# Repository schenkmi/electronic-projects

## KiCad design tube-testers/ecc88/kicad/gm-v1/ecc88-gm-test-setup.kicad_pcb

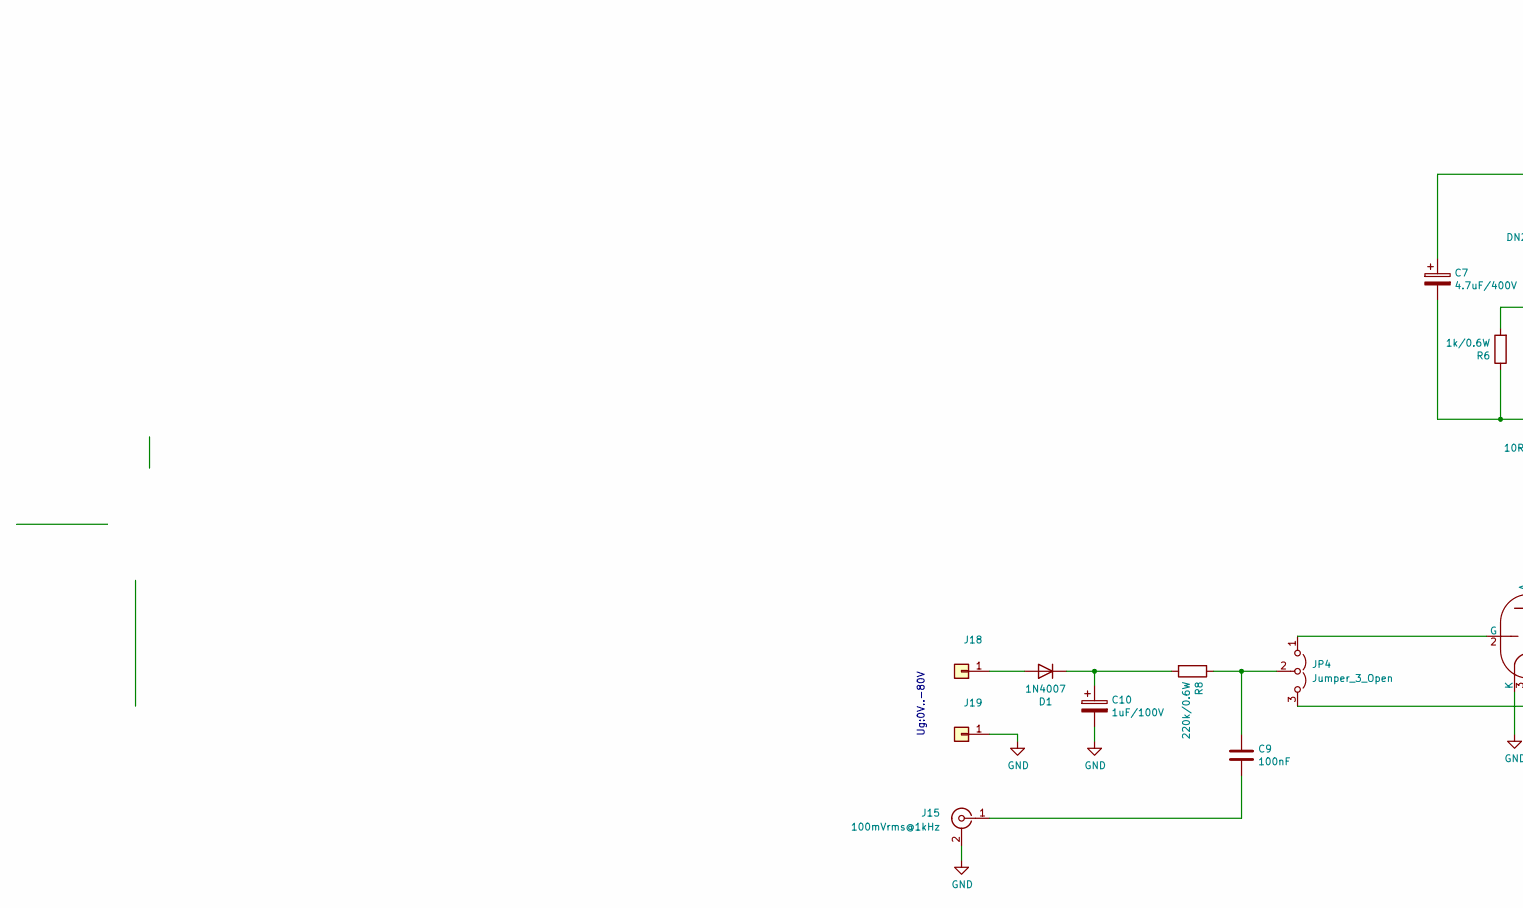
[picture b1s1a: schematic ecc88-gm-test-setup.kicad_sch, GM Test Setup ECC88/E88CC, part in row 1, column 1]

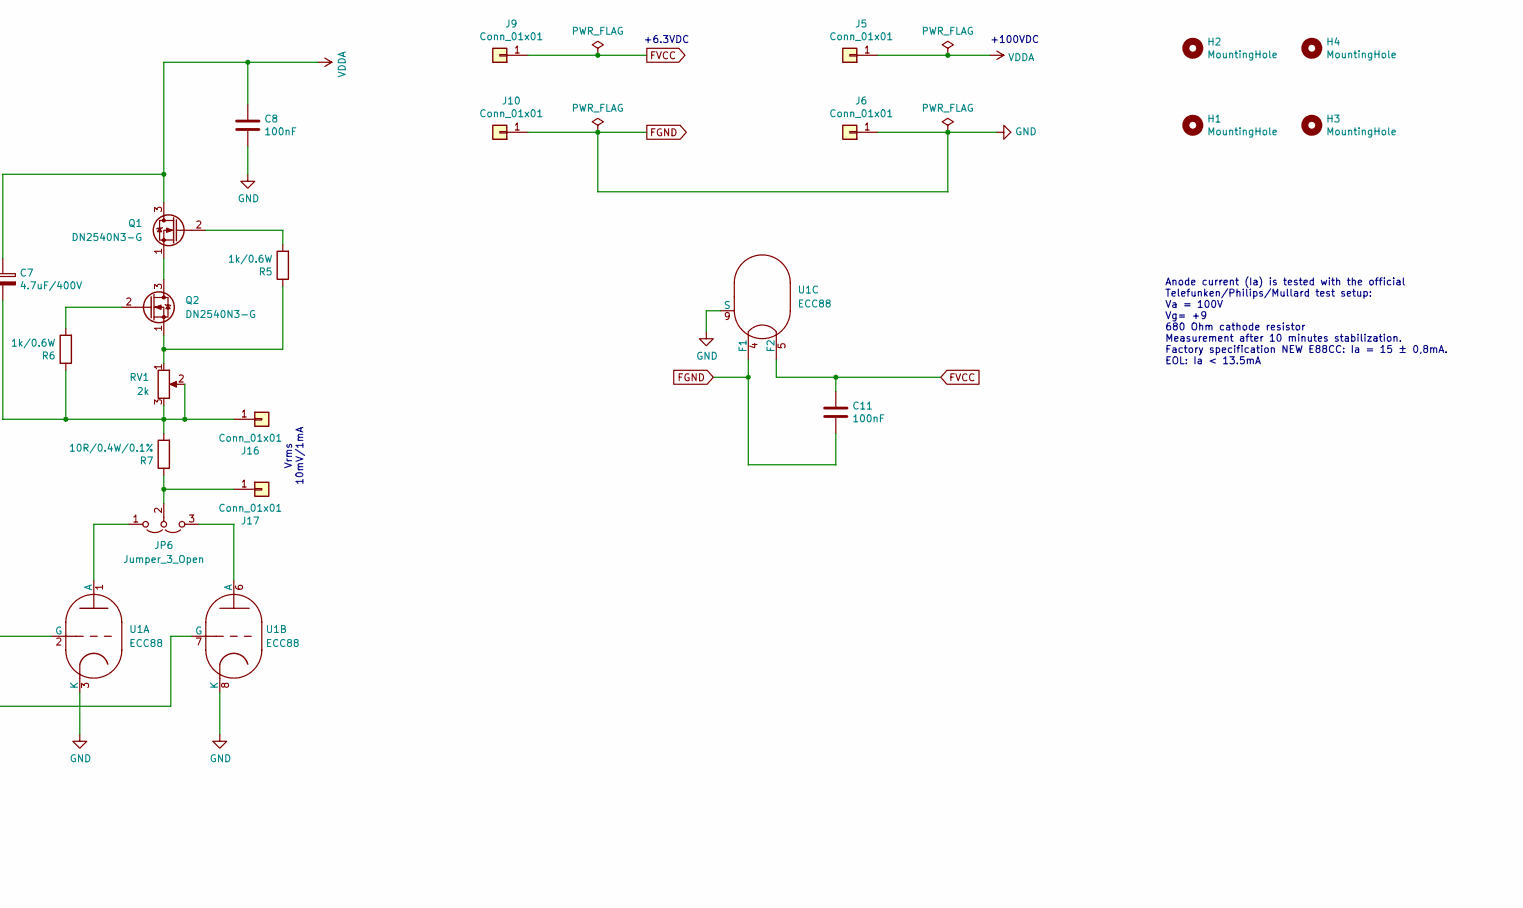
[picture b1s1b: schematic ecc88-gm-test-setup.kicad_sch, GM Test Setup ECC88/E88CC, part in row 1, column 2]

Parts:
C7: 4.7uF/400V; CP_Radial_D10.0mm_P5.00mm
C8: 100nF; C_Rect_L16.5mm_W5.0mm_P15.00mm_MKT
C9, C11: 100nF; C_Rect_L7.2mm_W2.5mm_P5.00mm_FKS2_FKP2_MKS2_MKP2
C10: 1uF/100V; CP_Radial_D5.0mm_P2.00mm
D1: 1N4007; D_DO-41_SOD81_P10.16mm_Horizontal
H1, H2, H3, H4: MountingHole; MountingHole_3.2mm_M3_Pad_Via
J5, J6, J9, J10: Conn_01x01; Pin_D1.3mm_L11.0mm
J15: 100mVrms@1kHz; RCA-Phono_CUI-Devices_RCJ-02X_Vertical
J16, J17: Conn_01x01; Pin_D1.0mm_L10.0mm
J18, J19: Pin_D1.0mm_L10.0mm
JP4, JP6: Jumper_3_Open; PinHeader_1x03_P2.54mm_Vertical
Q1, Q2: DN2540N3-G; TO-92_Inline
R5, R6: 1k/0.6W; R_Axial_DIN0207_L6.3mm_D2.5mm_P10.16mm_Horizontal
R7: 10R/0.4W/0.1%; R_Axial_DIN0207_L6.3mm_D2.5mm_P10.16mm_Horizontal
R8: 220k/0.6W; R_Axial_DIN0207_L6.3mm_D2.5mm_P10.16mm_Horizontal
RV1: 2k; Potentiometer_Bourns_3296W_Vertical
U1: ECC88; socket_gzc9-b

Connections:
FGND: C8.2, C10.2, C11.2, J6.1, J10.1, J15.2 (Ext), J19.1, U1.3 (K), U1.4 (F1), U1.8 (K), U1.9 (S)
FVCC: C11.1, J9.1, U1.5 (F2)
unnamed: D1.2 (A), J18.1
unnamed: C10.1, D1.1 (K), R8.2
unnamed: C9.2, J15.1 (In)
unnamed: C7.2, J16.1, R6.1, R7.2, RV1.2, RV1.3
unnamed: J17.1, JP6.2 (C), R7.1
unnamed: JP4.1 (A), U1.2 (G)
unnamed: JP4.3 (B), U1.7 (G)
unnamed: C9.1, JP4.2 (C), R8.1
unnamed: JP6.1 (A), U1.1 (A)
unnamed: JP6.3 (B), U1.6 (A)
unnamed: Q1.2 (G), R5.2
unnamed: Q1.1 (S), Q2.3 (D)
unnamed: Q2.2 (G), R6.2
unnamed: Q2.1 (S), R5.1, RV1.1
VDDA: C7.1, C8.1, J5.1, Q1.3 (D)

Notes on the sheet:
+6.3VDC
Anode current (Ia) is tested with the official Telefunken/Philips/Mullard test setup: Va = 100V Vg= +9 680 Ohm cathode resistor Measurement after 10 minutes stabilization. Factory specification NEW E88CC: Ia = 15 ± 0,8mA. EOL: Ia < 13.5mA
+100VDC
Vrms 10mV/1mA
Ug:0V..-80V

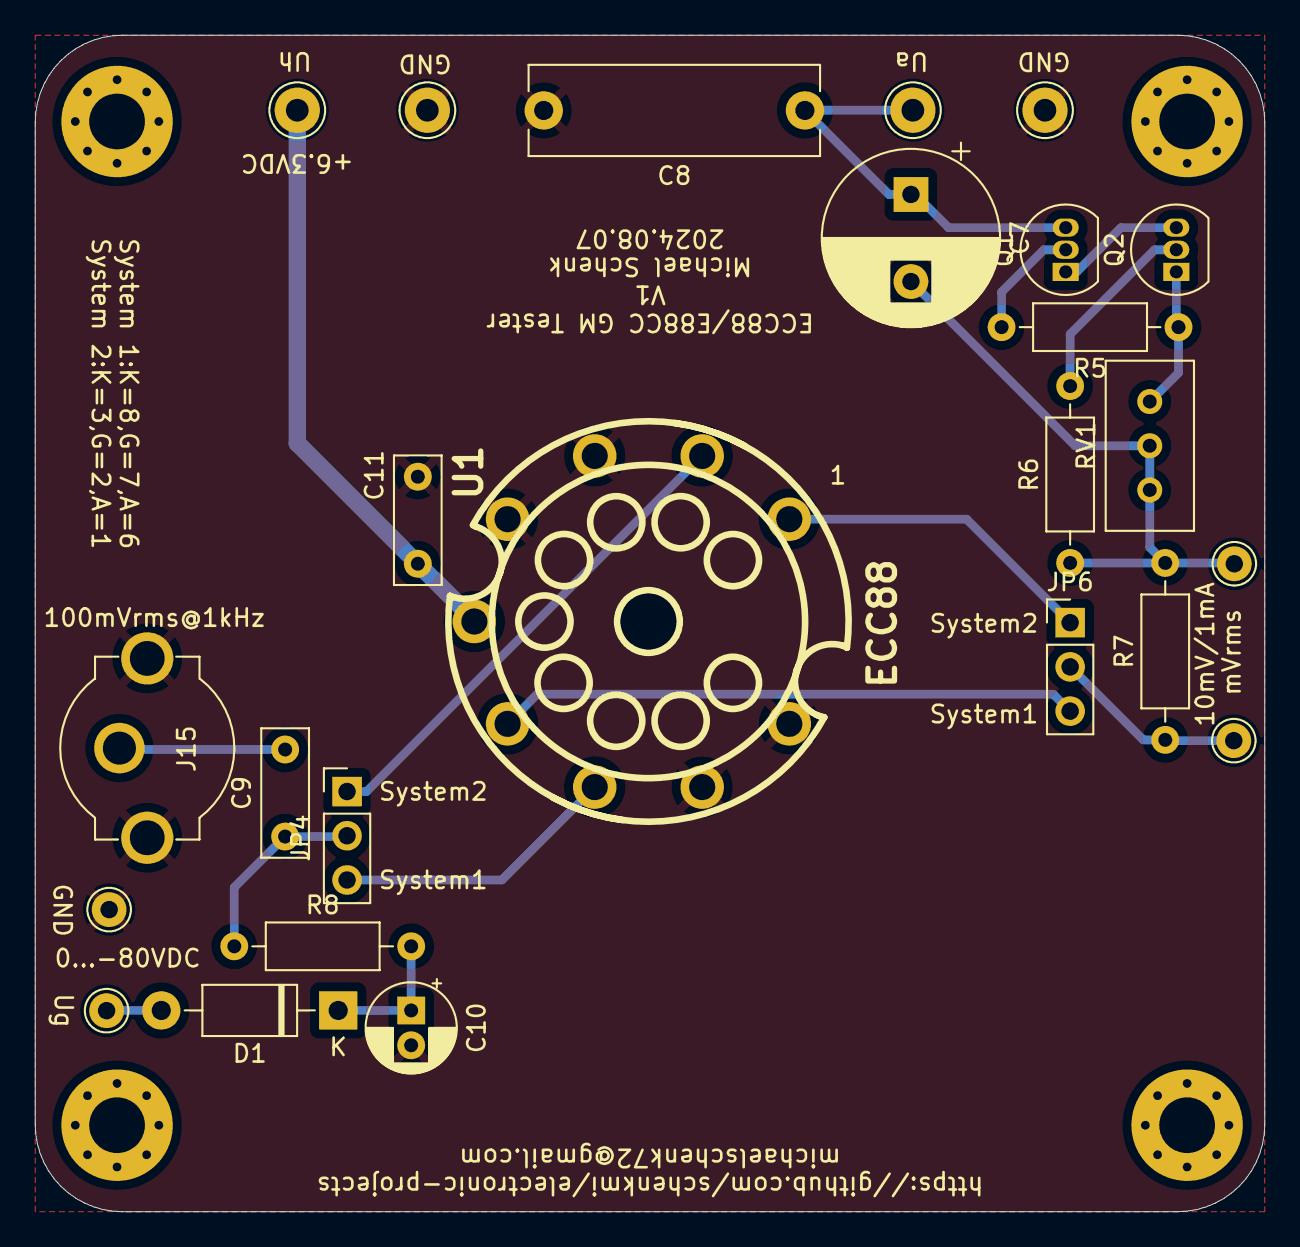
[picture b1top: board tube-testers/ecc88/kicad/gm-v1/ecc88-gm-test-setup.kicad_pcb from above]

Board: 2 copper layers, 70.6 x 67.6 mm, 29 parts (0 on the bottom side), 17 nets.

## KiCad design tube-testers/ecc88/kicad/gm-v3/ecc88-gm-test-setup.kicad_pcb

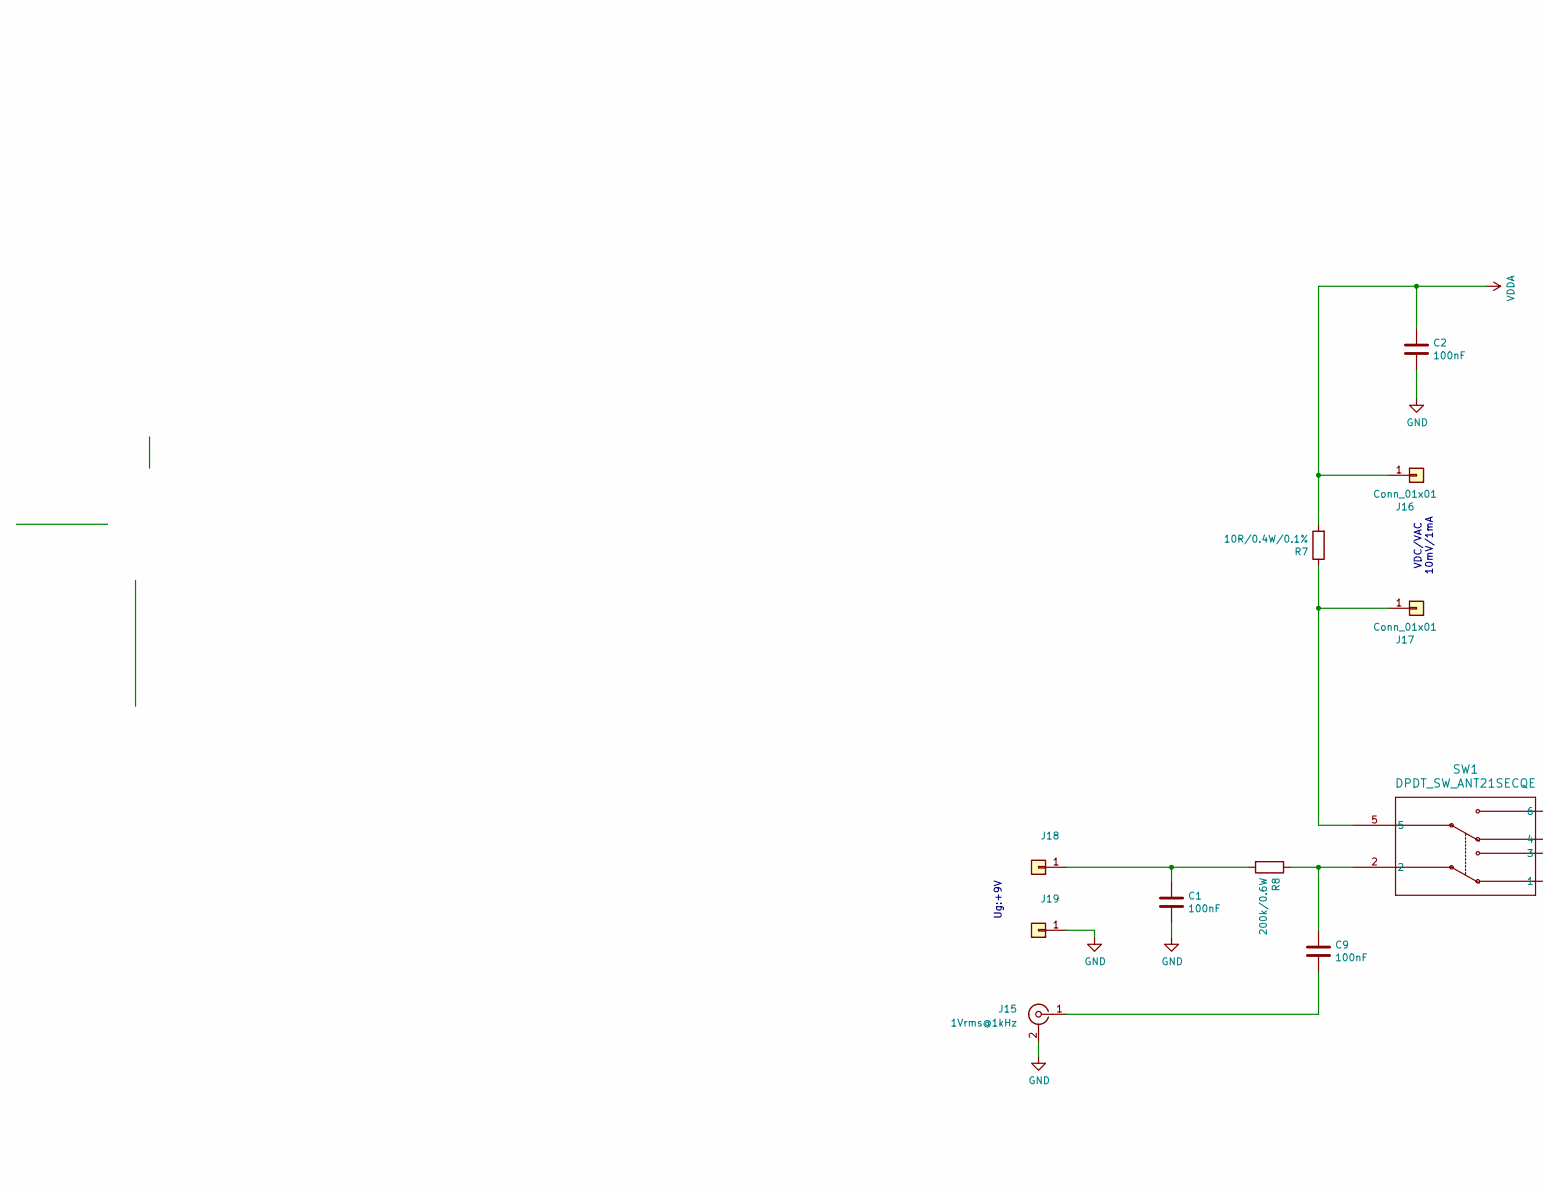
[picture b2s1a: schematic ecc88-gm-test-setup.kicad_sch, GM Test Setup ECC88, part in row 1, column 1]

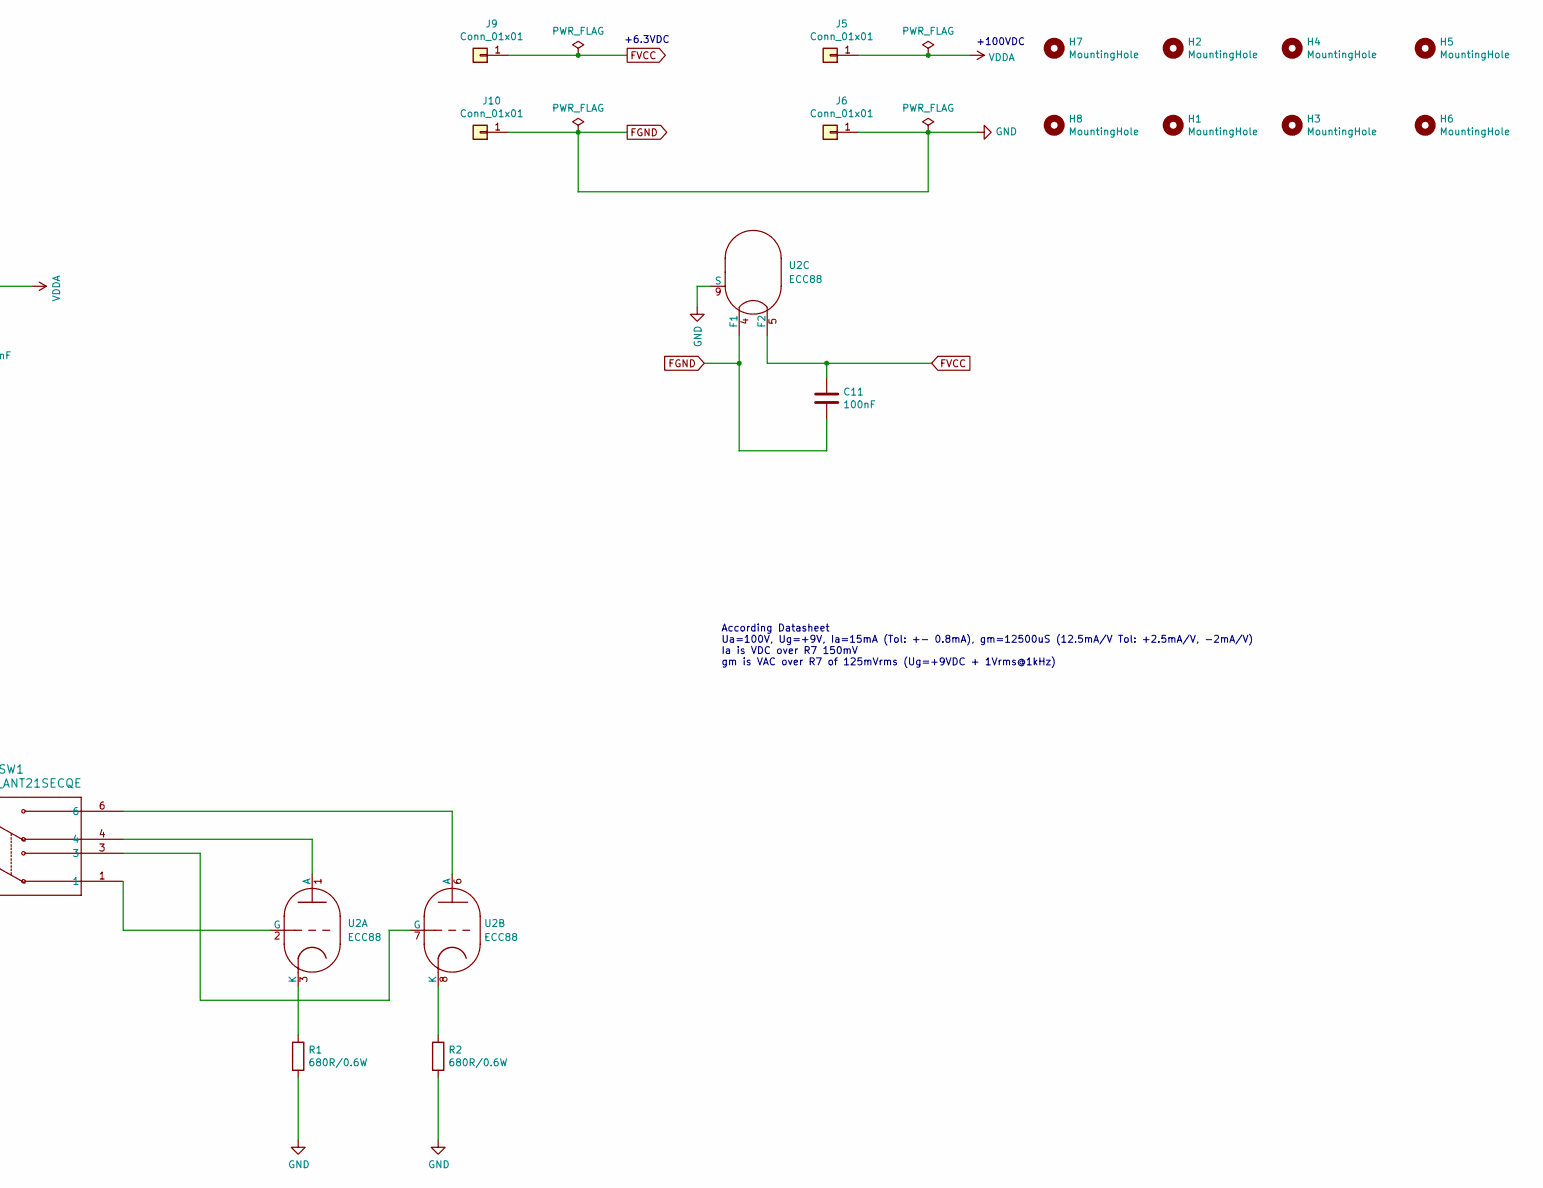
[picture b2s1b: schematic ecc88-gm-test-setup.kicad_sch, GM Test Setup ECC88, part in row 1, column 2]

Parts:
C1, C9, C11: 100nF; C_Rect_L7.2mm_W2.5mm_P5.00mm_FKS2_FKP2_MKS2_MKP2
C2: 100nF; C_Rect_L16.5mm_W5.0mm_P15.00mm_MKT
H1, H2, H3, H4, H5, H6, H7, H8: MountingHole; MountingHole_3.2mm_M3_Pad_Via
J5, J6, J9, J10: Conn_01x01; Pin_D1.3mm_L11.0mm
J15: 1Vrms@1kHz; RCA-Phono_CUI-Devices_RCJ-02X_Vertical
J16, J17: Conn_01x01; Pin_D1.0mm_L10.0mm
J18, J19: Pin_D1.0mm_L10.0mm
R1, R2: 680R/0.6W; R_Axial_DIN0207_L6.3mm_D2.5mm_P10.16mm_Horizontal
R7: 10R/0.4W/0.1%; R_Axial_DIN0207_L6.3mm_D2.5mm_P10.16mm_Horizontal
R8: 200k/0.6W; R_Axial_DIN0207_L6.3mm_D2.5mm_P10.16mm_Horizontal
SW1: DPDT_SW_ANT21SECQE; SW6_ANT21SECQE_CRS
U2: ECC88; TubeNoval-ECC88

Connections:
FGND: C1.2, C2.2, C11.2, J6.1, J10.1, J15.2 (Ext), J19.1, R1.2, R2.2, U2.4 (F1), U2.9 (S)
FVCC: C11.1, J9.1, U2.5 (F2)
unnamed: C9.1, R8.1, SW1.2
unnamed: C9.2, J15.1 (In)
unnamed: J17.1, R7.1, SW1.5
unnamed: C1.1, J18.1, R8.2
unnamed: SW1.4, U2.1 (A)
unnamed: SW1.1, U2.2 (G)
unnamed: R1.1, U2.3 (K)
unnamed: SW1.6, U2.6 (A)
unnamed: SW1.3, U2.7 (G)
unnamed: R2.1, U2.8 (K)
VDDA: C2.1, J5.1, J16.1, R7.2

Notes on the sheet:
+6.3VDC
VDC/VAC 10mV/1mA
Ug:+9V
According Datasheet Ua=100V, Ug=+9V, Ia=15mA (Tol: +- 0.8mA), gm=12500uS (12.5mA/V Tol: +2.5mA/V, -2mA/V) Ia is VDC over R7 150mV gm is VAC over R7 of 125mVrms (Ug=+9VDC + 1Vrms@1kHz)
+100VDC

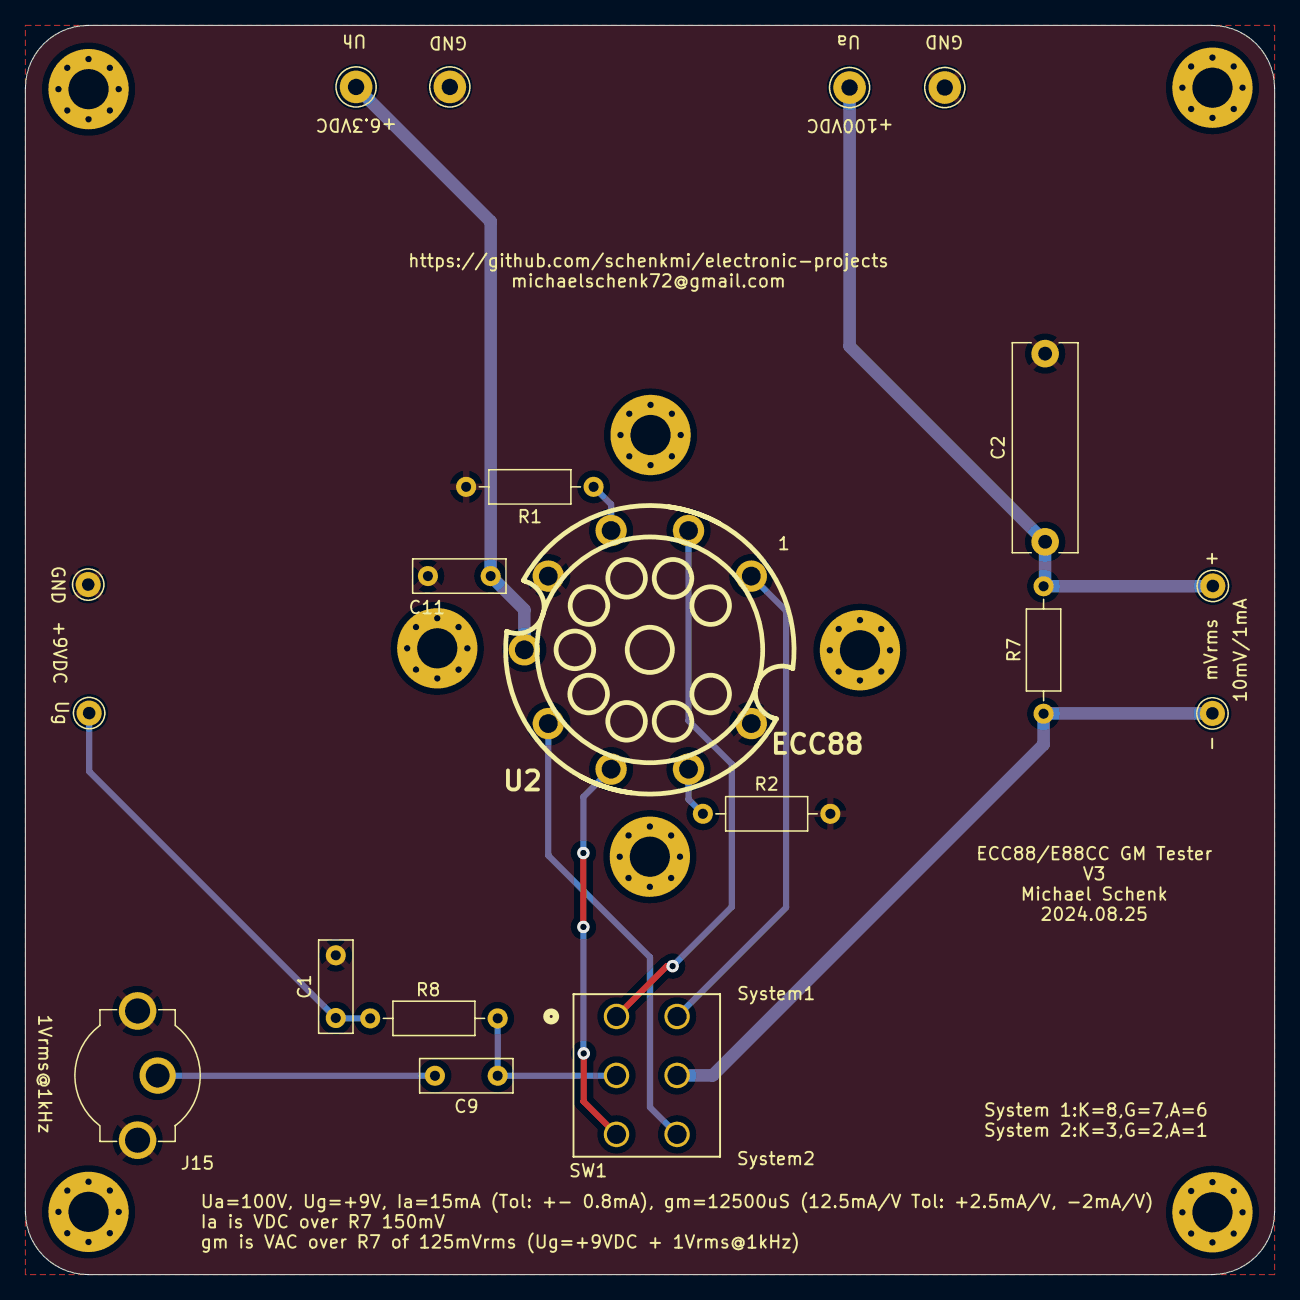
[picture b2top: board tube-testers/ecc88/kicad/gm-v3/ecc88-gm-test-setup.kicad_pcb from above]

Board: 2 copper layers, 99.6 x 99.6 mm, 27 parts (0 on the bottom side), 13 nets.

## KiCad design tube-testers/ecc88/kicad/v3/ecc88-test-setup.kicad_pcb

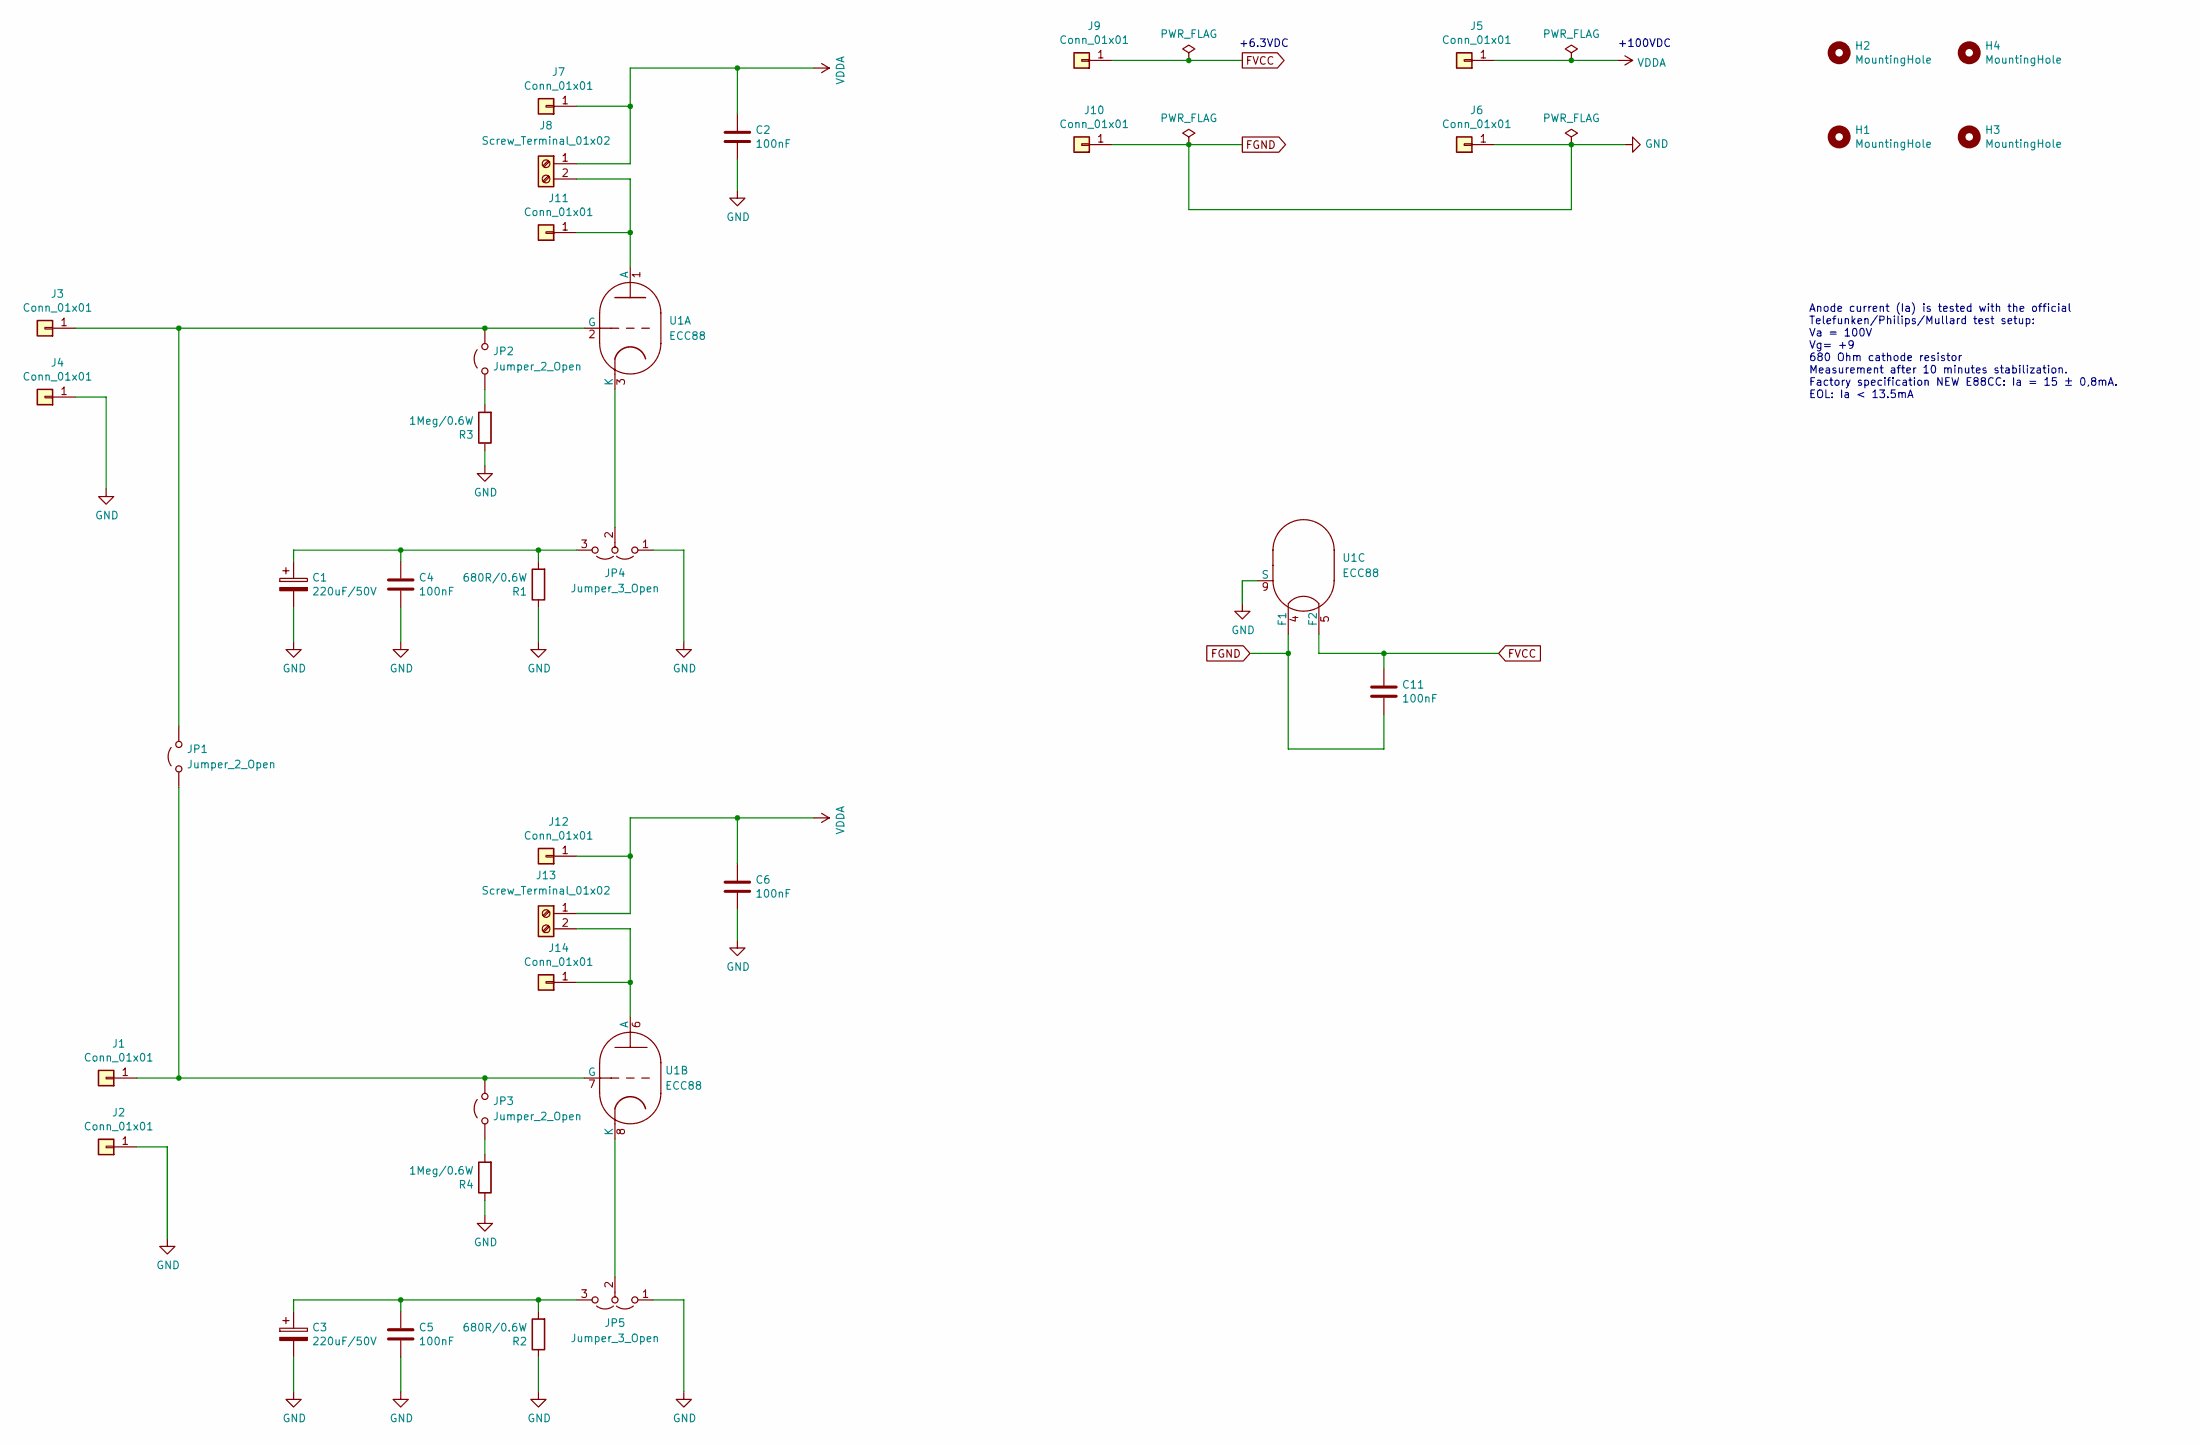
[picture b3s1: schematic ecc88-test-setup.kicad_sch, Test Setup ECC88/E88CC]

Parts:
C1, C3: 220uF/50V; CP_Radial_D8.0mm_P3.50mm
C2, C6: 100nF; C_Rect_L16.5mm_W5.0mm_P15.00mm_MKT
C4, C5, C11: 100nF; C_Rect_L7.2mm_W2.5mm_P5.00mm_FKS2_FKP2_MKS2_MKP2
H1, H2, H3, H4: MountingHole; MountingHole_3.2mm_M3_Pad_Via
J1, J2, J3, J4, J7, J11, J12, J14: Conn_01x01; Pin_D1.0mm_L10.0mm
J5, J6, J9, J10: Conn_01x01; Pin_D1.3mm_L11.0mm
J8, J13: Screw_Terminal_01x02; TerminalBlock_RND_205-00012_1x02_P5.00mm_Horizontal
JP1, JP2, JP3: Jumper_2_Open; PinHeader_1x02_P2.54mm_Vertical
JP4, JP5: Jumper_3_Open; PinHeader_1x03_P2.54mm_Vertical
R1, R2: 680R/0.6W; R_Axial_DIN0207_L6.3mm_D2.5mm_P10.16mm_Horizontal
R3, R4: 1Meg/0.6W; R_Axial_DIN0207_L6.3mm_D2.5mm_P10.16mm_Horizontal
U1: ECC88; socket_gzc9-b

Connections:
FGND: C1.2, C2.2, C3.2, C4.2, C5.2, C6.2, C11.2, J2.1, J4.1, J6.1, J10.1, JP4.1 (A), JP5.1 (A), R1.1, R2.1, R3.1, R4.1, U1.4 (F1), U1.9 (S)
FVCC: C11.1, J9.1, U1.5 (F2)
unnamed: J1.1, JP1.1 (A), JP3.2 (B), U1.7 (G)
unnamed: J3.1, JP1.2 (B), JP2.2 (B), U1.2 (G)
unnamed: J8.2, J11.1, U1.1 (A)
unnamed: J13.2, J14.1, U1.6 (A)
unnamed: JP2.1 (A), R3.2
unnamed: JP3.1 (A), R4.2
unnamed: C1.1, C4.1, JP4.3 (B), R1.2
unnamed: JP4.2 (C), U1.3 (K)
unnamed: C3.1, C5.1, JP5.3 (B), R2.2
unnamed: JP5.2 (C), U1.8 (K)
VDDA: C2.1, C6.1, J5.1, J7.1, J8.1, J12.1, J13.1

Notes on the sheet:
+6.3VDC
Anode current (Ia) is tested with the official Telefunken/Philips/Mullard test setup: Va = 100V Vg= +9 680 Ohm cathode resistor Measurement after 10 minutes stabilization. Factory specification NEW E88CC: Ia = 15 ± 0,8mA. EOL: Ia < 13.5mA
+100VDC

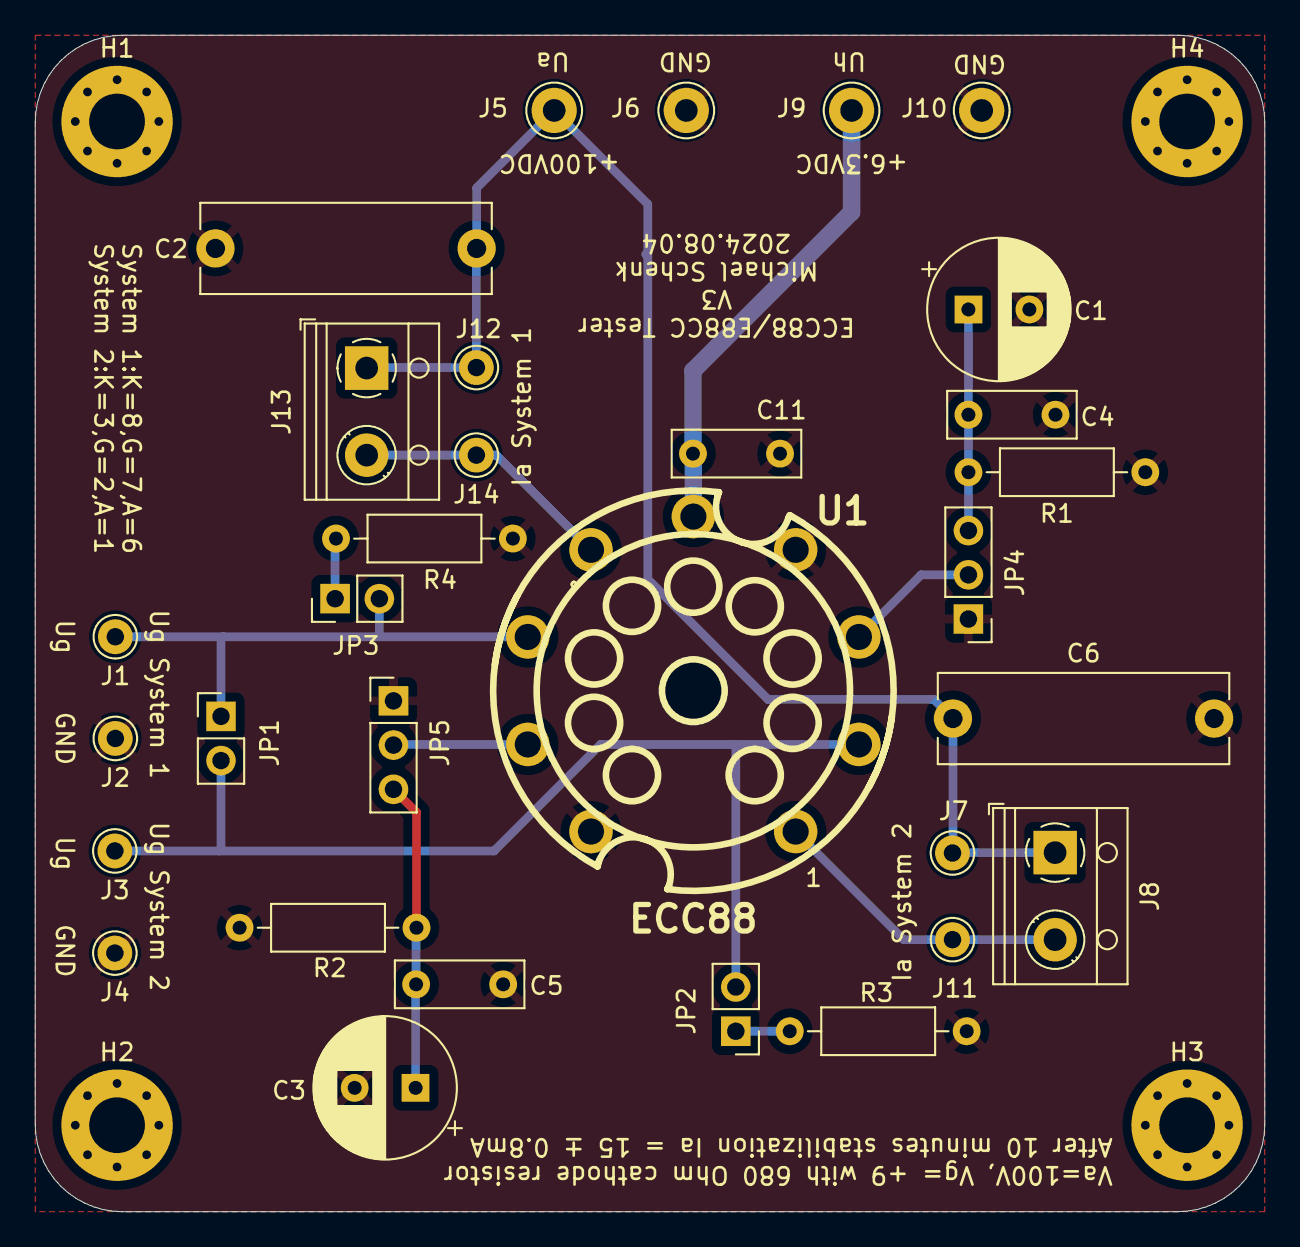
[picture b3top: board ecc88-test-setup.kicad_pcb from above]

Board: 2 copper layers, 70.6 x 67.6 mm, 35 parts (0 on the bottom side), 13 nets.

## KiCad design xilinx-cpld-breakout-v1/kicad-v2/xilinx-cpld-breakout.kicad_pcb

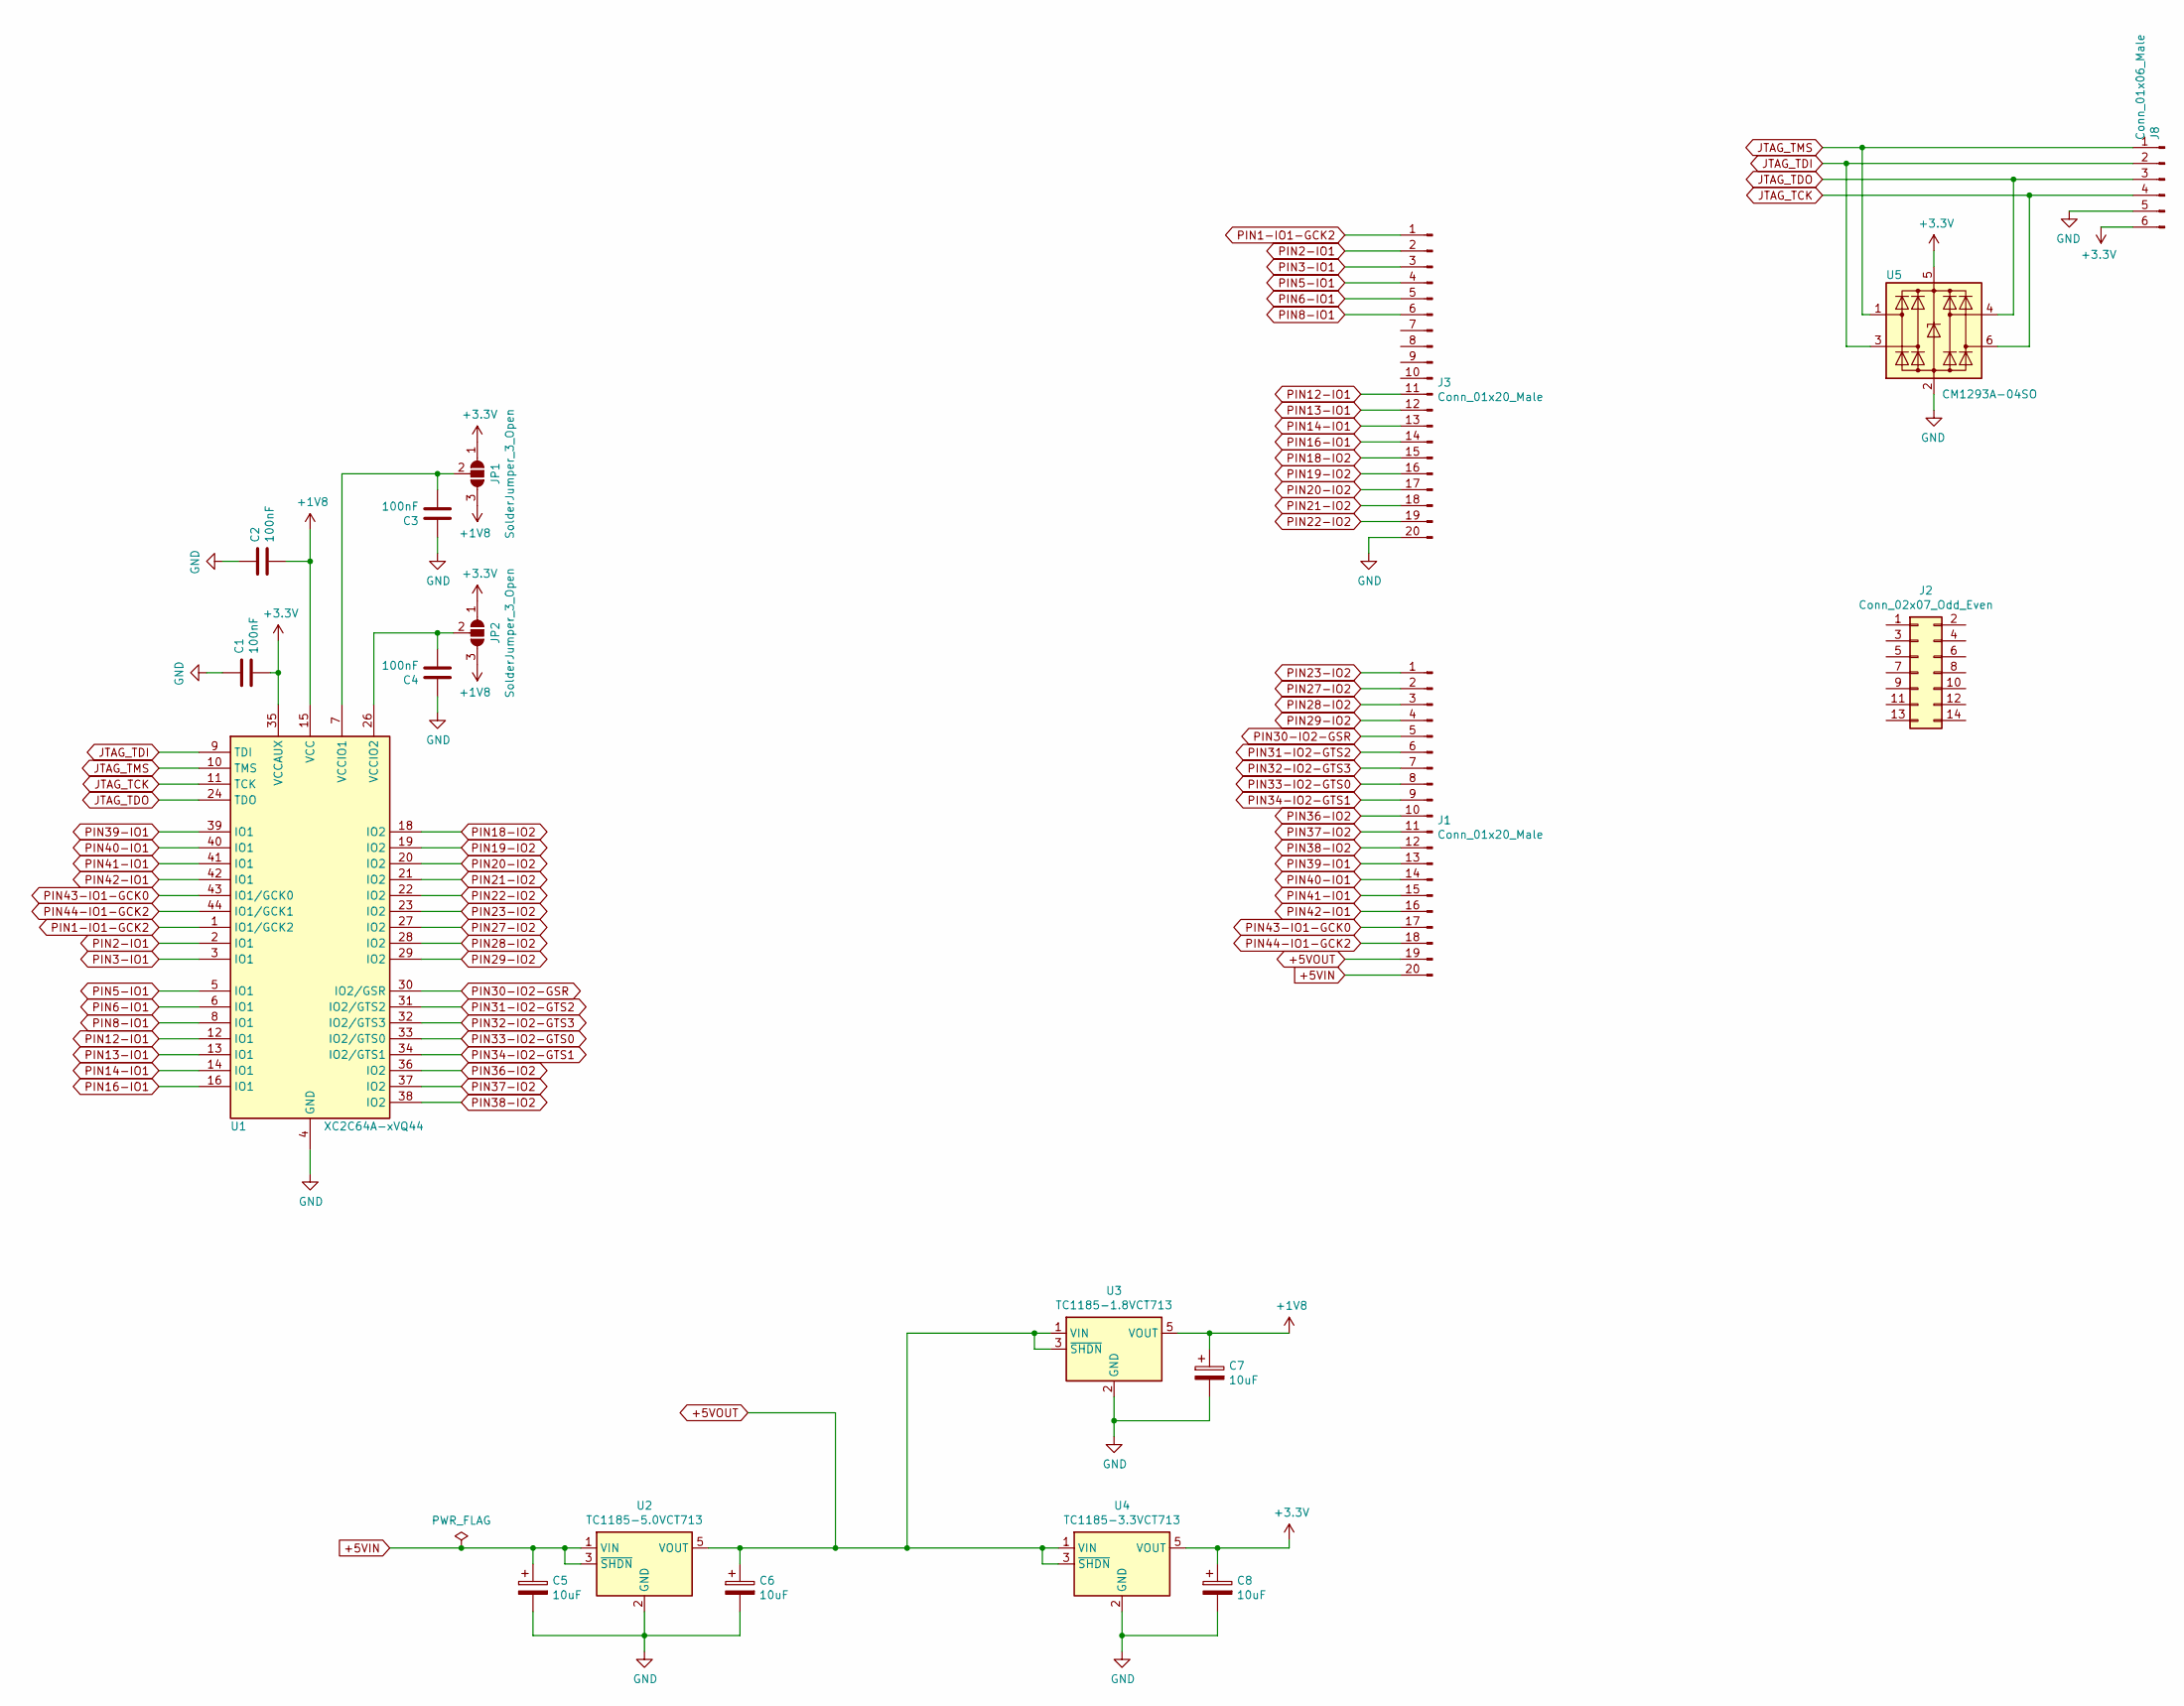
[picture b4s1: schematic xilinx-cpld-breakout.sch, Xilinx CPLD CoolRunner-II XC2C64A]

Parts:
C1, C2, C3, C4: 100nF; C_0603_1608Metric_Pad1.08x0.95mm_HandSolder
C5: 10uF; CP_EIA-3528-21_Kemet-B_Pad1.50x2.35mm_HandSolder
C6, C7, C8: 10uF; C_0805_2012Metric_Pad1.18x1.45mm_HandSolder
J1, J3: Conn_01x20_Male; PinHeader_1x20_P2.54mm_Vertical
J2: Conn_02x07_Odd_Even; PinHeader_2x07_P2.00mm_Vertical
J8: Conn_01x06_Male; PinHeader_1x06_P2.54mm_Vertical
JP1, JP2: SolderJumper_3_Open; SolderJumper-3_P1.3mm_Open_RoundedPad1.0x1.5mm_NumberLabels
U1: XC2C64A-xVQ44; TQFP-44_10x10mm_P0.8mm
U2: TC1185-5.0VCT713; SOT-23-5
U3: TC1185-1.8VCT713; SOT-23-5
U4: TC1185-3.3VCT713; SOT-23-5
U5: CM1293A−04SO; SC-74-6_1.5x2.9mm_P0.95mm

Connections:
+1V8: C2.2, C7.1, JP1.3 (B), JP2.3 (B), U1.15 (VCC), U3.5 (VOUT)
+3V3: C1.2, C8.1, J8.6, JP1.1 (A), JP2.1 (A), U1.35 (VCCAUX), U4.5 (VOUT), U5.5 (VBUS)
+5VIN: C5.1, J1.20, U2.1 (VIN), U2.3 (~SHDN)
+5VOUT: C6.1, J1.19, U2.5 (VOUT), U3.1 (VIN), U3.3 (~SHDN), U4.1 (VIN), U4.3 (~SHDN)
GND: C1.1, C2.1, C3.1, C4.1, C5.2, C6.2, C7.2, C8.2, J3.20, J8.5, U1.4 (GND), U1.17 (GND), U1.25 (GND), U2.2 (GND), U3.2 (GND), U4.2 (GND), U5.2 (GND)
JTAG_TCK: J8.4, U1.11 (TCK), U5.6 (I/O4)
JTAG_TDI: J8.2, U1.9 (TDI), U5.3 (I/O2)
JTAG_TDO: J8.3, U1.24 (TDO), U5.4 (I/O3)
JTAG_TMS: J8.1, U1.10 (TMS), U5.1 (I/O1)
unnamed: C3.2, JP1.2 (C), U1.7 (VCCIO1)
unnamed: C4.2, JP2.2 (C), U1.26 (VCCIO2)
PIN1-IO1-GCK2: J3.1, U1.1 (IO1/GCK2)
PIN2-IO1: J3.2, U1.2 (IO1)
PIN3-IO1: J3.3, U1.3 (IO1)
PIN5-IO1: J3.4, U1.5 (IO1)
PIN6-IO1: J3.5, U1.6 (IO1)
PIN8-IO1: J3.6, U1.8 (IO1)
PIN12-IO1: J3.11, U1.12 (IO1)
PIN13-IO1: J3.12, U1.13 (IO1)
PIN14-IO1: J3.13, U1.14 (IO1)
PIN16-IO1: J3.14, U1.16 (IO1)
PIN18-IO2: J3.15, U1.18 (IO2)
PIN19-IO2: J3.16, U1.19 (IO2)
PIN20-IO2: J3.17, U1.20 (IO2)
PIN21-IO2: J3.18, U1.21 (IO2)
PIN22-IO2: J3.19, U1.22 (IO2)
PIN23-IO2: J1.1, U1.23 (IO2)
PIN27-IO2: J1.2, U1.27 (IO2)
PIN28-IO2: J1.3, U1.28 (IO2)
PIN29-IO2: J1.4, U1.29 (IO2)
PIN30-IO2-GSR: J1.5, U1.30 (IO2/GSR)
PIN31-IO2-GTS2: J1.6, U1.31 (IO2/GTS2)
PIN32-IO2-GTS3: J1.7, U1.32 (IO2/GTS3)
PIN33-IO2-GTS0: J1.8, U1.33 (IO2/GTS0)
PIN34-IO2-GTS1: J1.9, U1.34 (IO2/GTS1)
PIN36-IO2: J1.10, U1.36 (IO2)
PIN37-IO2: J1.11, U1.37 (IO2)
PIN38-IO2: J1.12, U1.38 (IO2)
PIN39-IO1: J1.13, U1.39 (IO1)
PIN40-IO1: J1.14, U1.40 (IO1)
PIN41-IO1: J1.15, U1.41 (IO1)
PIN42-IO1: J1.16, U1.42 (IO1)
PIN43-IO1-GCK0: J1.17, U1.43 (IO1/GCK0)
PIN44-IO1-GCK2: J1.18, U1.44 (IO1/GCK1)
